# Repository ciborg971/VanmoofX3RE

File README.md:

# VanmoofX3RE

Big WIP, build at your own risk

- [OG contains information about original hardware](OG/README.md)

- [OSHW-Version is a fully open source redesign of the smart cardridge and battery BMS](OSHW-Version/README.md)

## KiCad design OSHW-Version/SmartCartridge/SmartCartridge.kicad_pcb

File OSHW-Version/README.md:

The led display is glued to the housing, charging port + original charger communication protocol will be hard to reverse, SIM slot + gsm antenna + backup battery are not needed so ... going for a 3D printed Smart Housing !

## 3D design of the smart cartridge housing

Still WIP
 
Online preview https://collaborate.shapr3d.com/v/ECH1UW3ffuTfgxgP5jvtE

All the cad is made on Shapr3d, if you need a file in a specific format create a github issue.

## BMS

Need to find compatible connector + cell specification

## SmartCartridge

Use the Pro-S3 from Unexpected Maker and I'm using [their kicad lib](https://github.com/UnexpectedMaker/esp32s3/tree/main)

Need to find compatible connector

Back 8 pin connector signals :

- GND
- Back light
- NC
- NC
- NC
- NC
- NC
- NC

Top front 10 pin connector signals :

- unknown
- unknown
- unknown
- GND
- unknown
- GND
- GND
- unknown
- unknown
- GND

Bottom front 12 pin connector signals :

- unknown
- GND
- unknown
- unknown
- unknown
- unknown
- GND
- unknown
- unknown
- unknown
- unknown
- unknown

Bottom front 10 pin connector signals :

- unknown
- GND
- unknown
- GND
- GND
- unknown
- unknown
- unknown
- GND
- unknown

## LedDisplay

166 WS2812-2020 RGB led (flexible pcb)
5V@6A peak

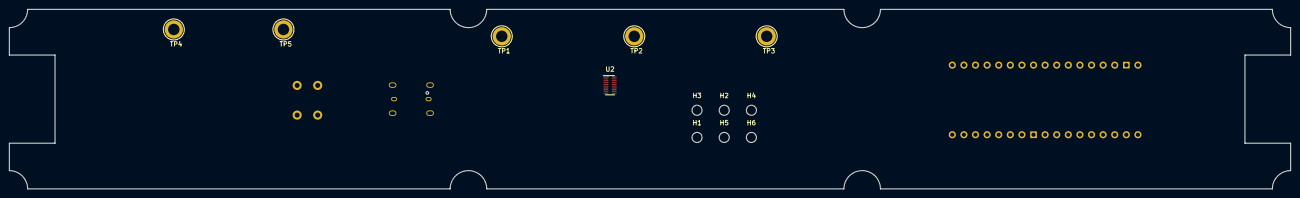
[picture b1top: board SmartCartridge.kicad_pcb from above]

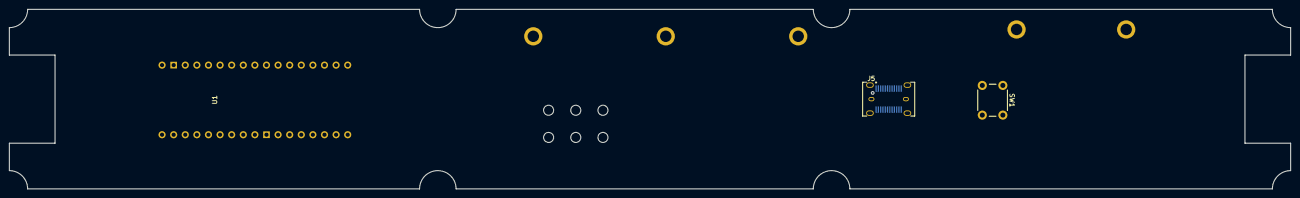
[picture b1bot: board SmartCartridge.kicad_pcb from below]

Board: 2 copper layers, 280.5 x 39.3 mm, 15 parts (3 on the bottom side), 2 nets, no tracks yet.

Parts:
H1, H2, H3, H4, H5, H6: MountingHole; MountingHole_2.2mm_M2
J5: USB_C_Receptacle; USB_C_Receptacle_JAE_DX07S024WJ1R350
SW1: SW_Push; SW_PUSH_6mm
TP1: BL1; TestPoint_Loop_D3.80mm_Drill2.5mm
TP2: BL2; TestPoint_Loop_D3.80mm_Drill2.5mm
TP3: BL3; TestPoint_Loop_D3.80mm_Drill2.5mm
TP4: VBAT-; TestPoint_Loop_D3.80mm_Drill2.5mm
TP5: VBAT+; TestPoint_Loop_D3.80mm_Drill2.5mm
U1: ProS3; ProS3_TH
U2: TXB0108DQSR; USON-20_2x4mm_P0.4mm

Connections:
unnamed: J5.A1 (GND), J5.A12 (GND), J5.B1 (GND), J5.B12 (GND)
unnamed: J5.A4 (VBUS), J5.A9 (VBUS), J5.B4 (VBUS), J5.B9 (VBUS)

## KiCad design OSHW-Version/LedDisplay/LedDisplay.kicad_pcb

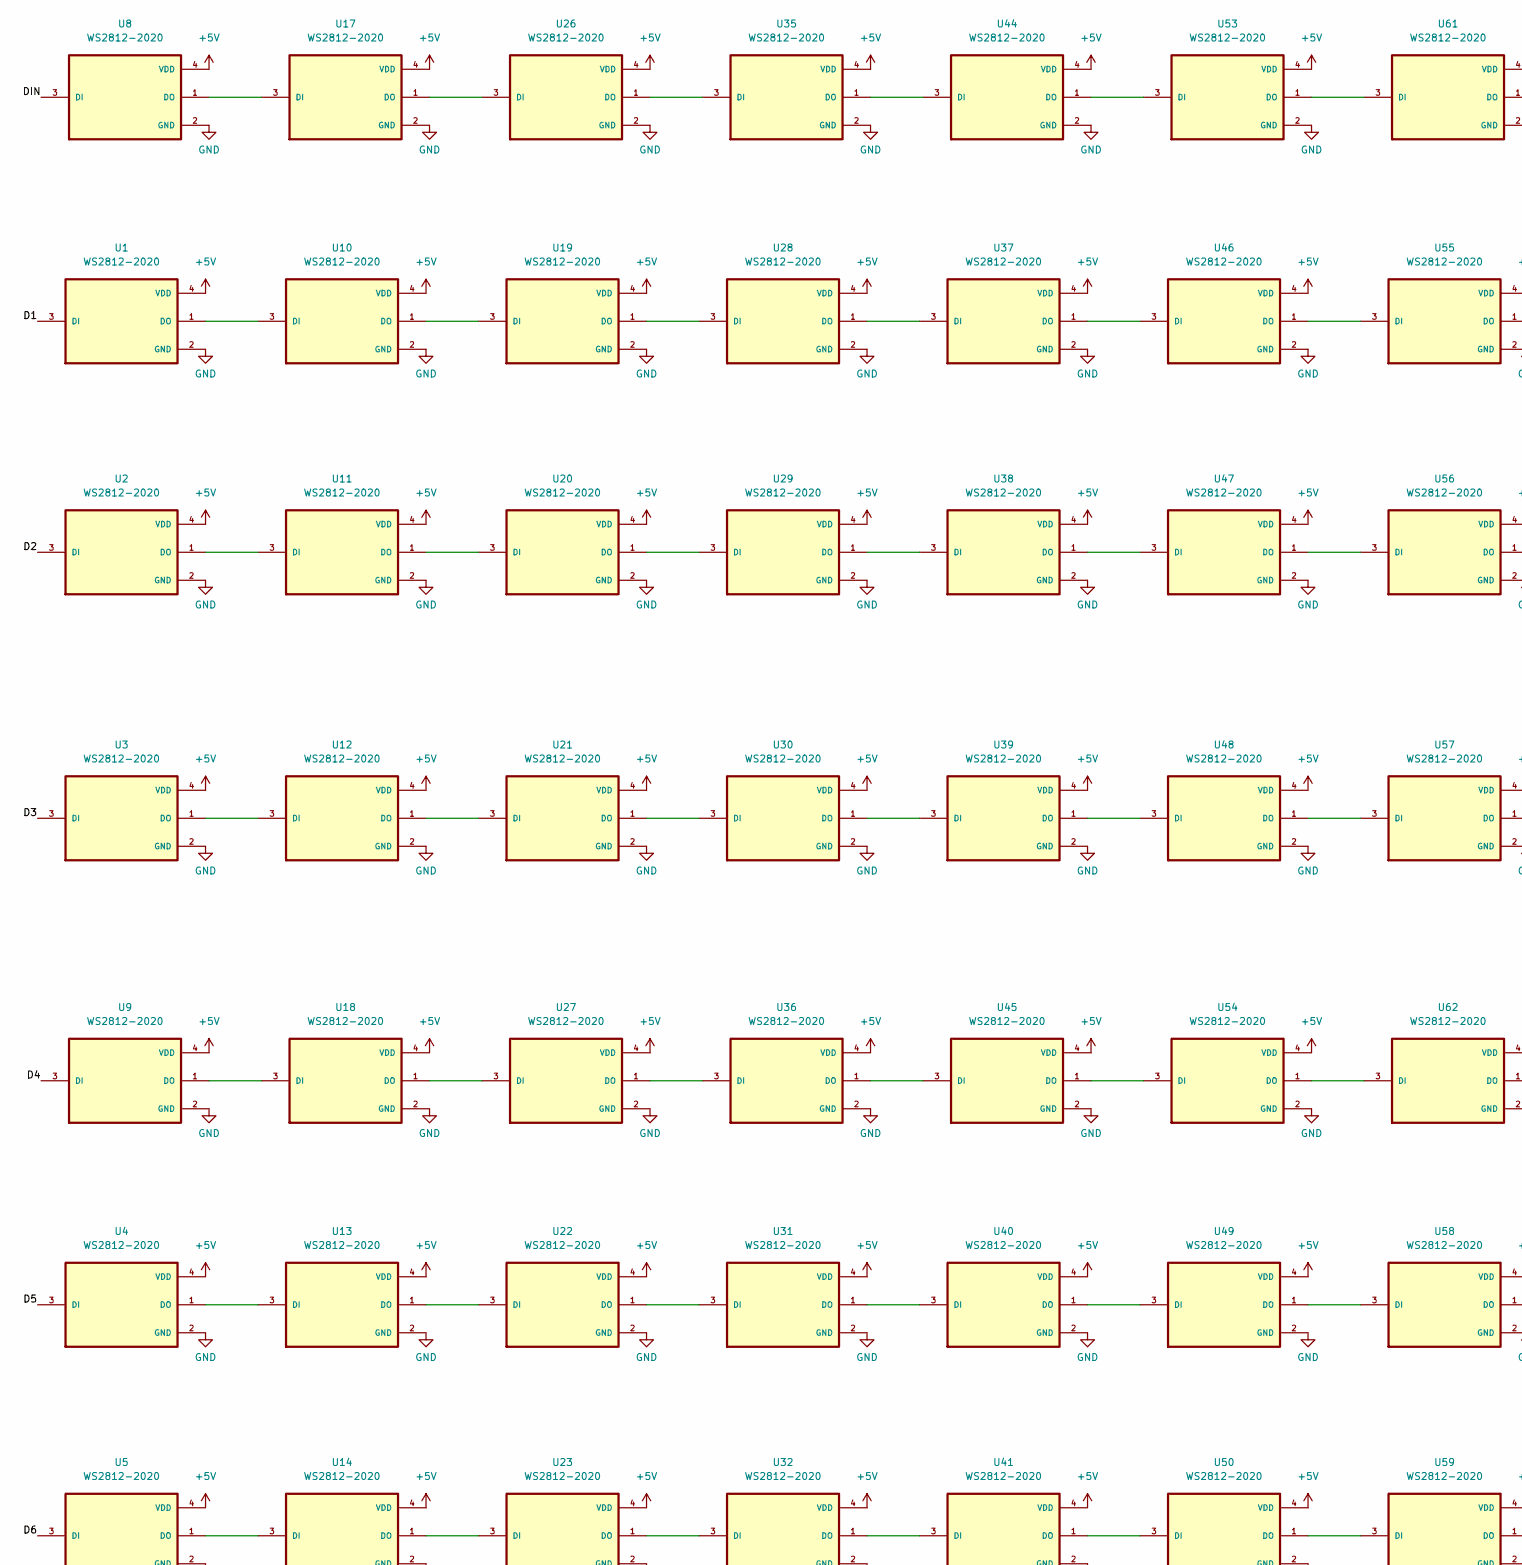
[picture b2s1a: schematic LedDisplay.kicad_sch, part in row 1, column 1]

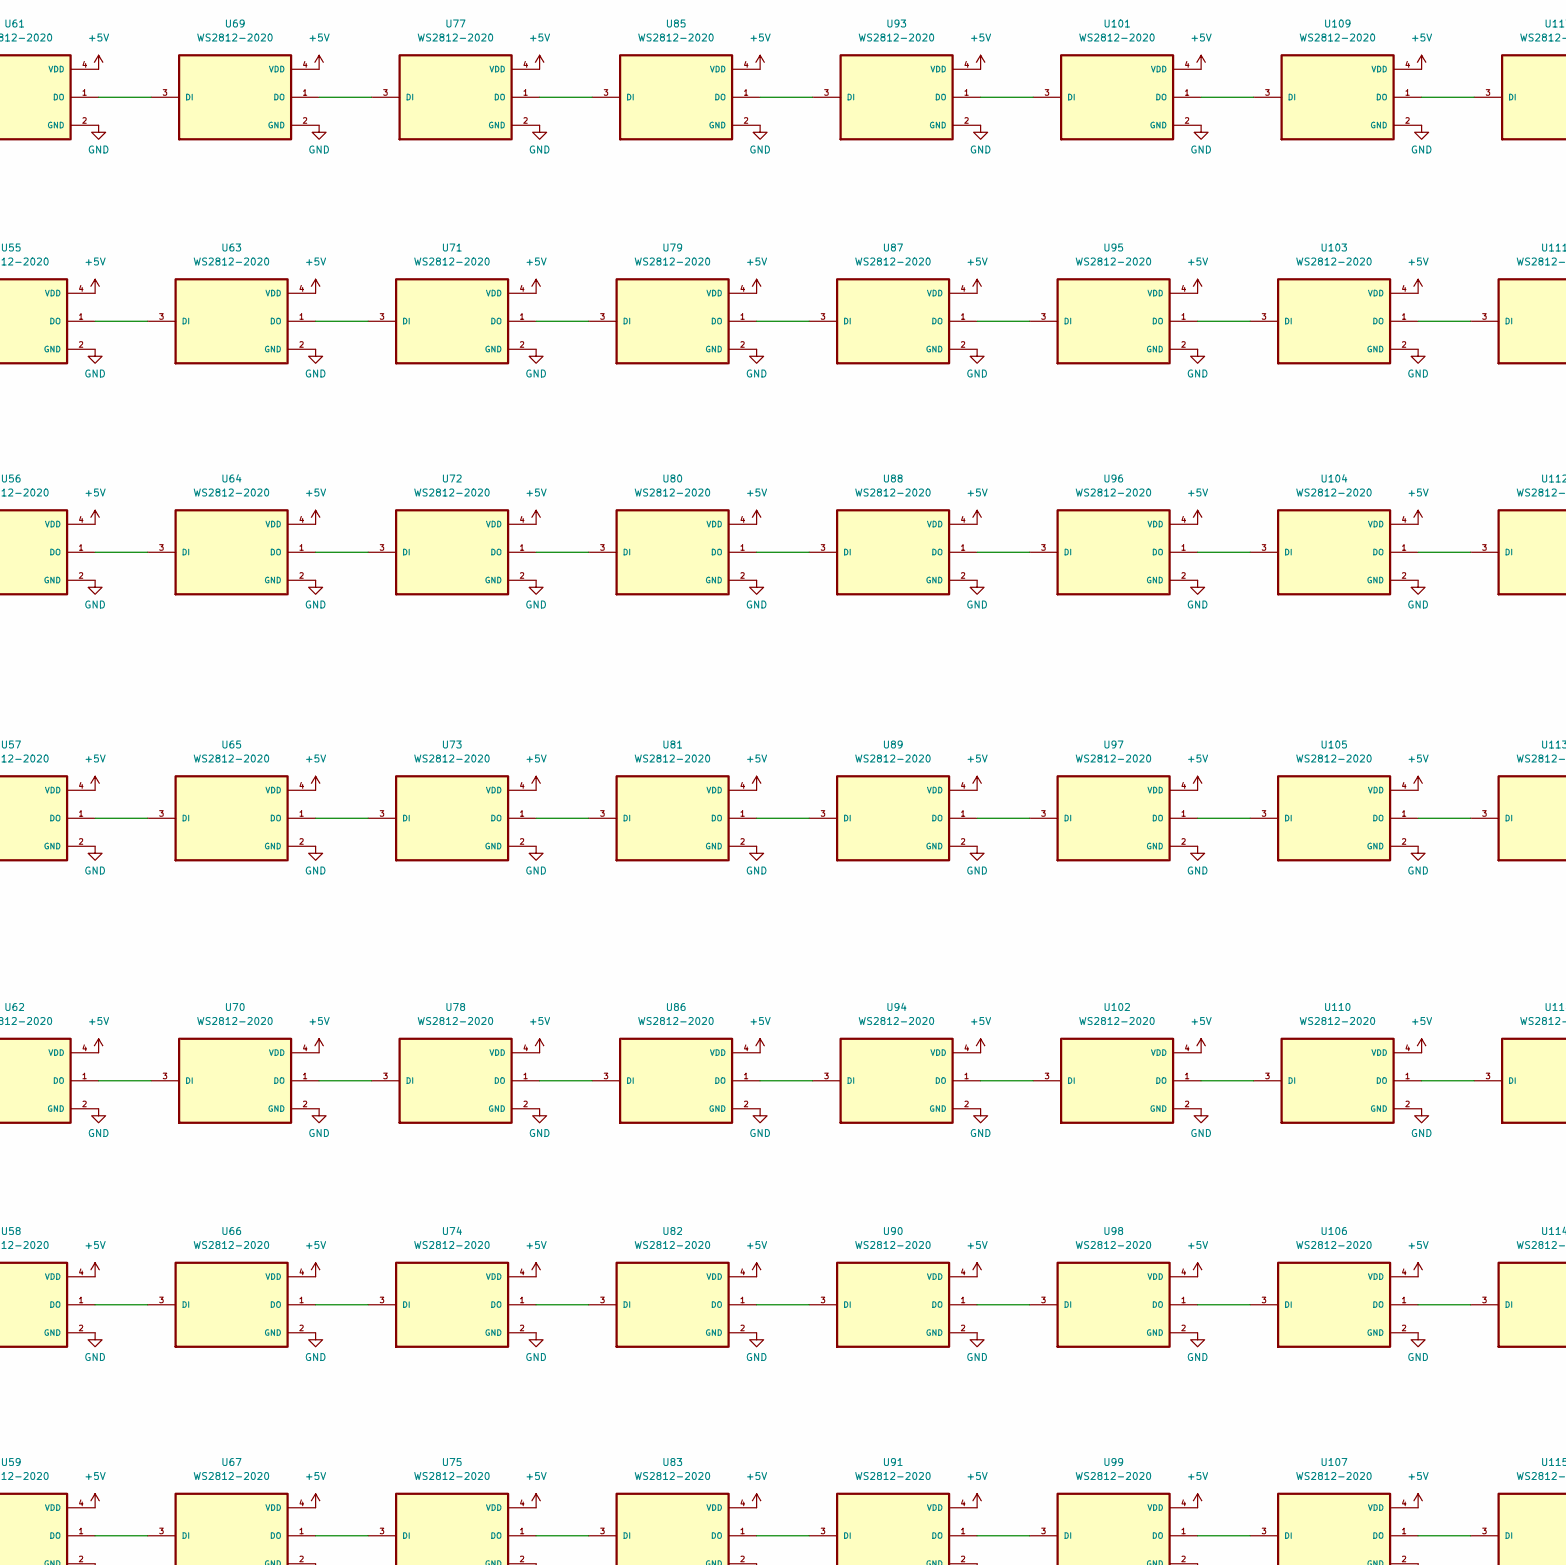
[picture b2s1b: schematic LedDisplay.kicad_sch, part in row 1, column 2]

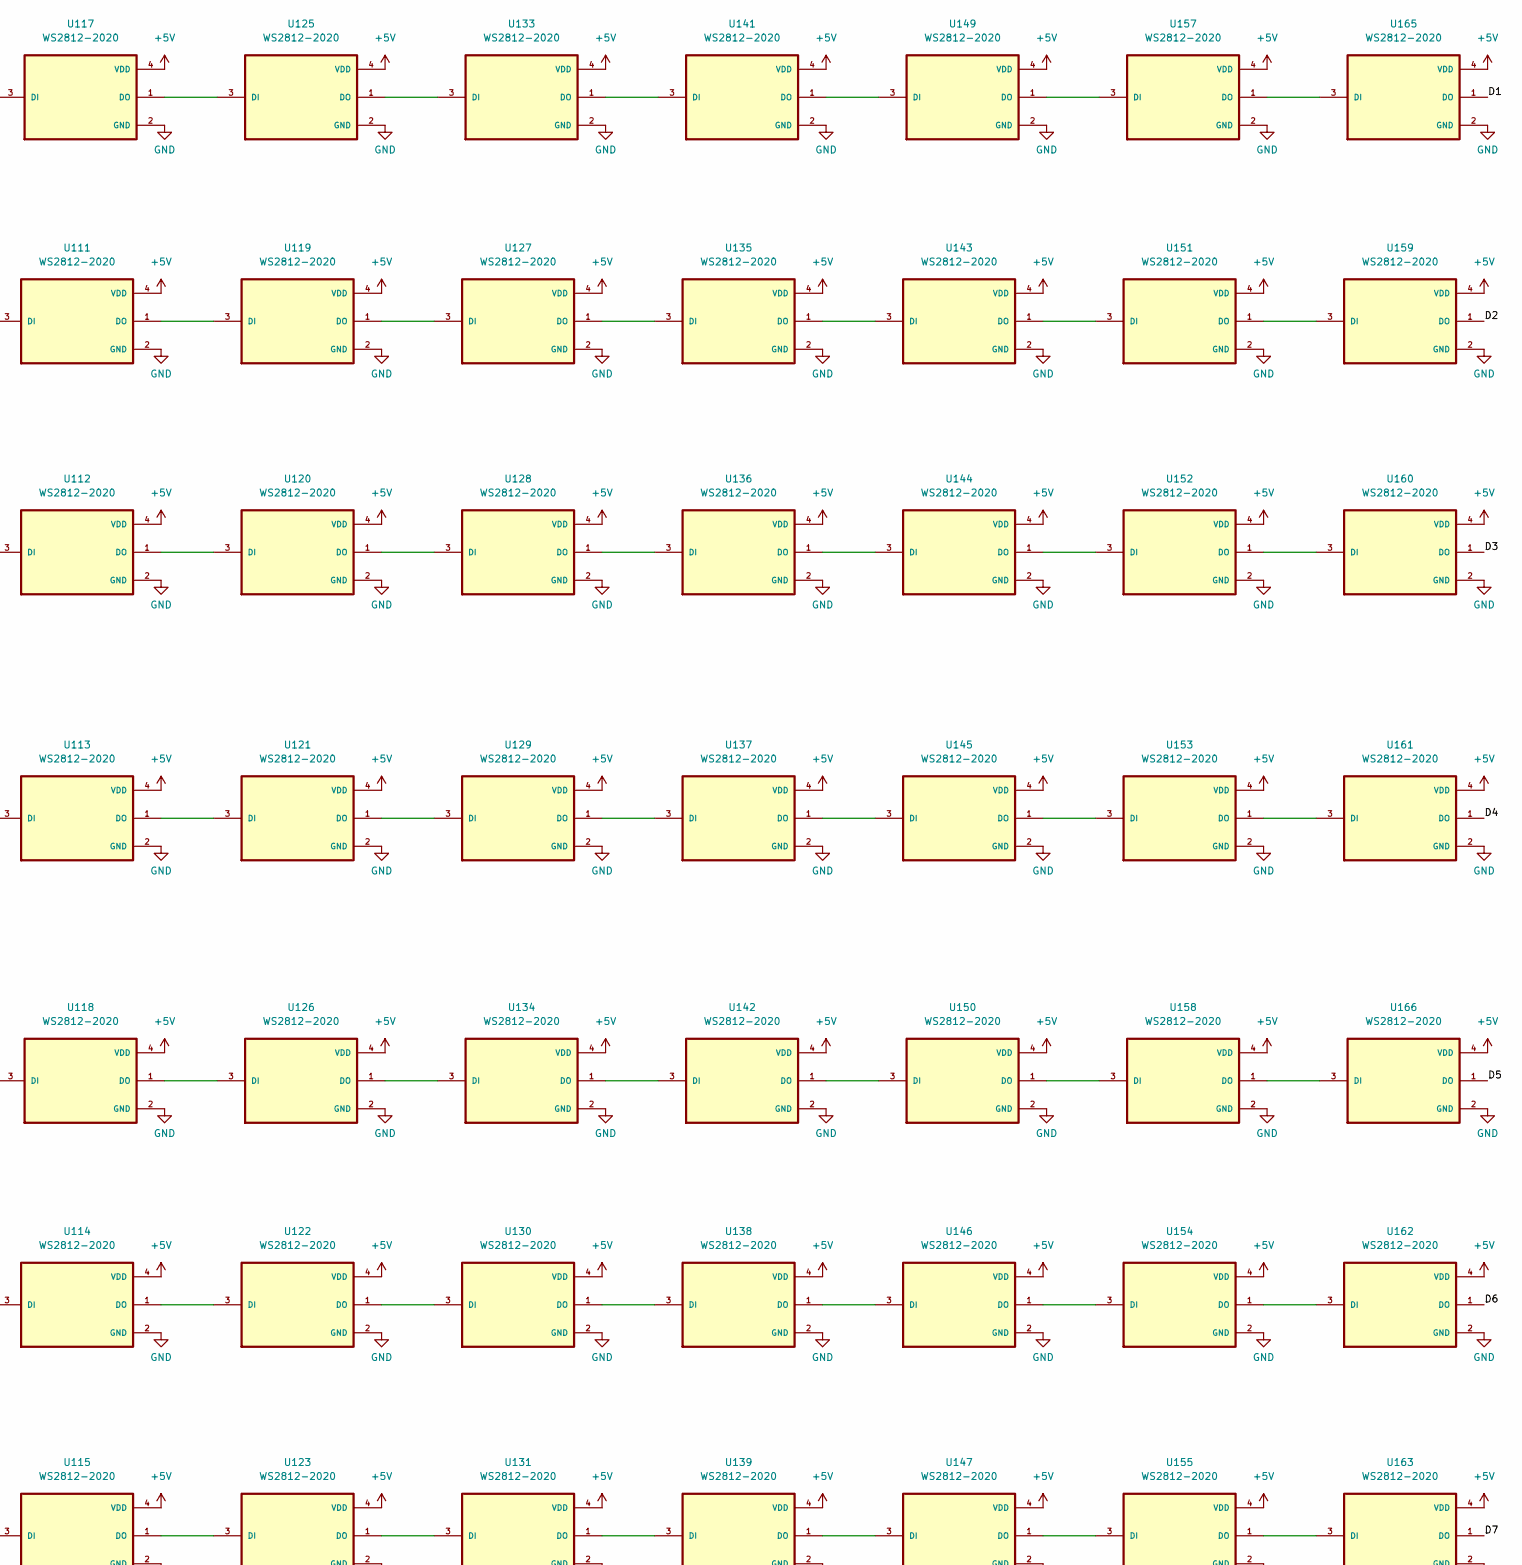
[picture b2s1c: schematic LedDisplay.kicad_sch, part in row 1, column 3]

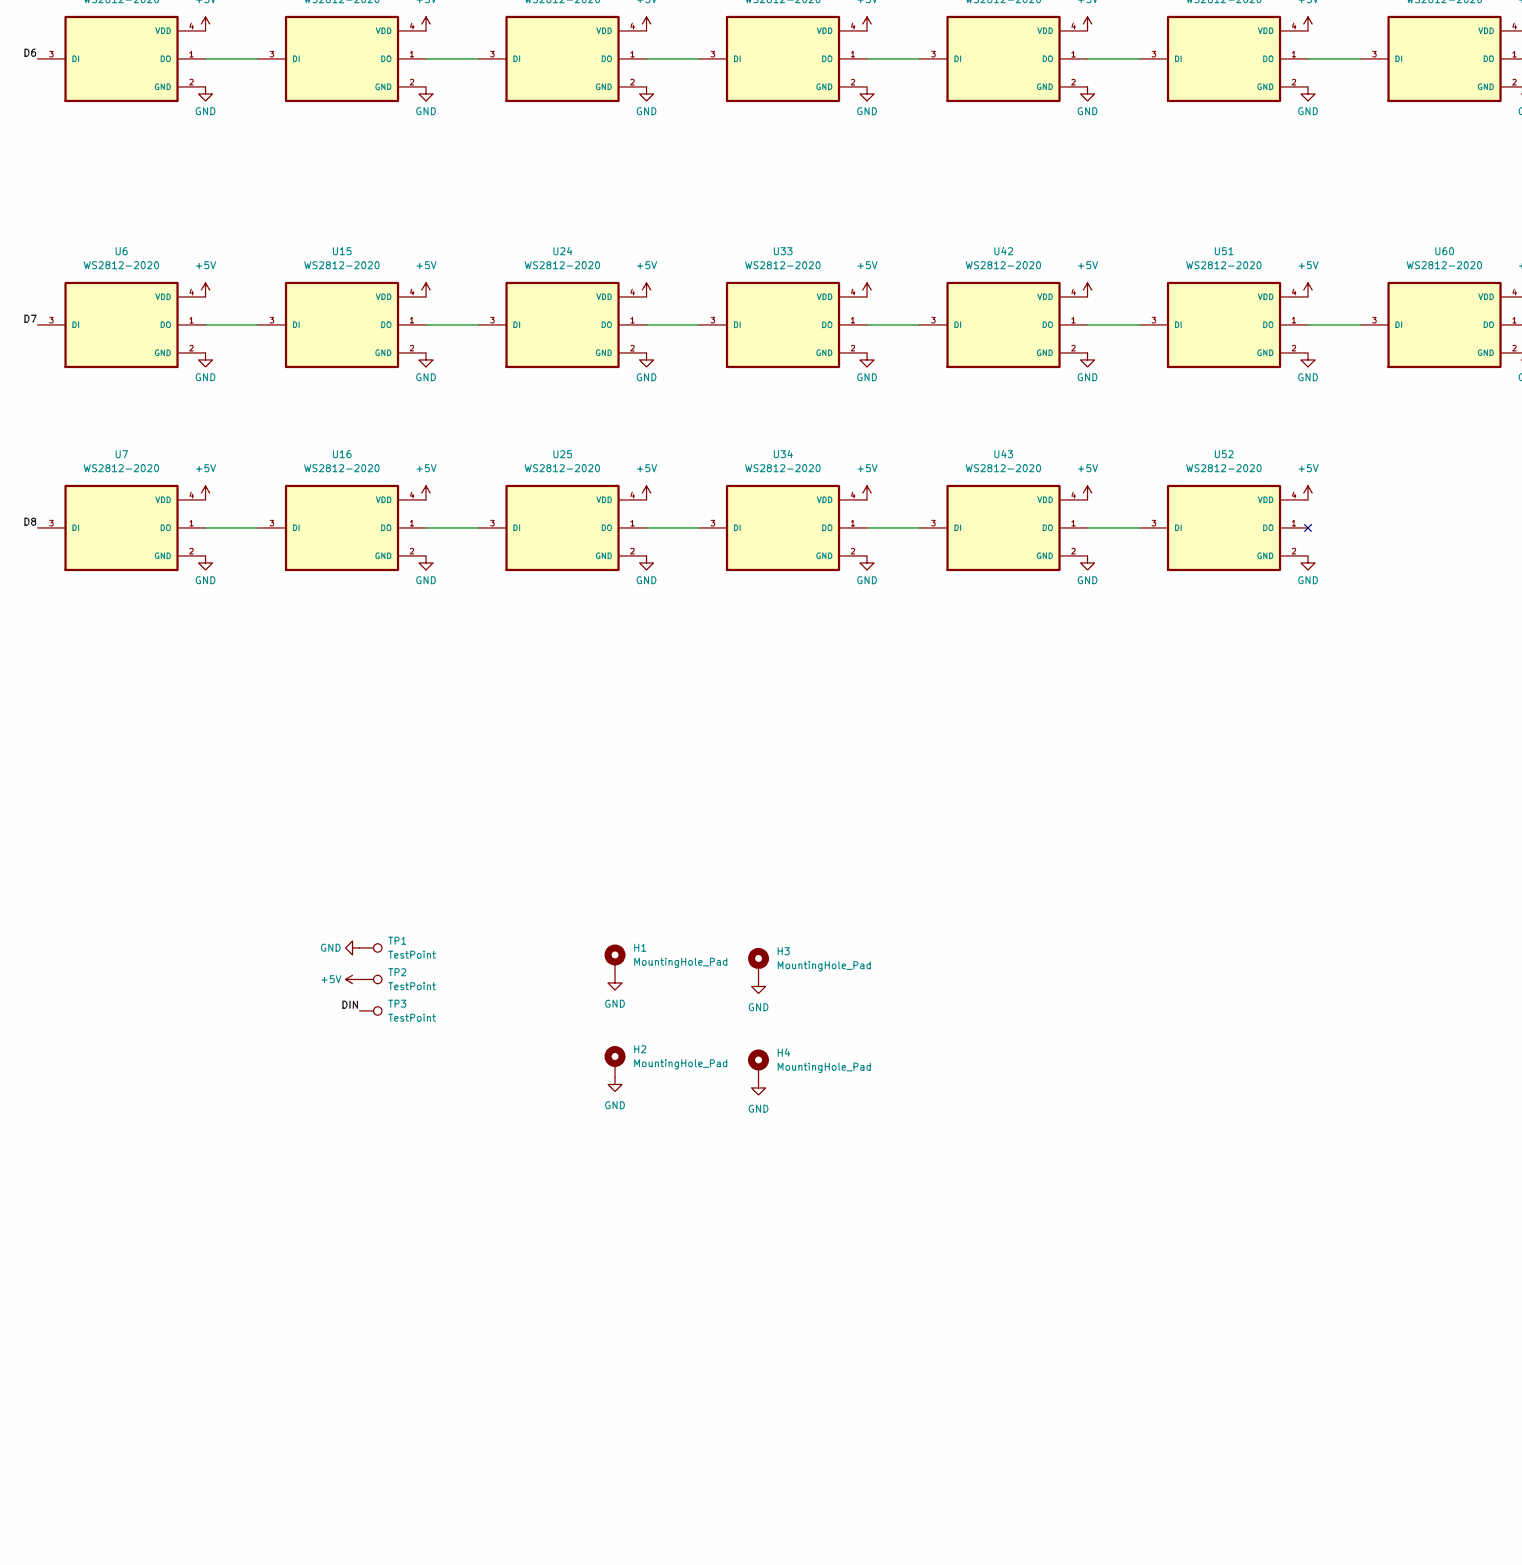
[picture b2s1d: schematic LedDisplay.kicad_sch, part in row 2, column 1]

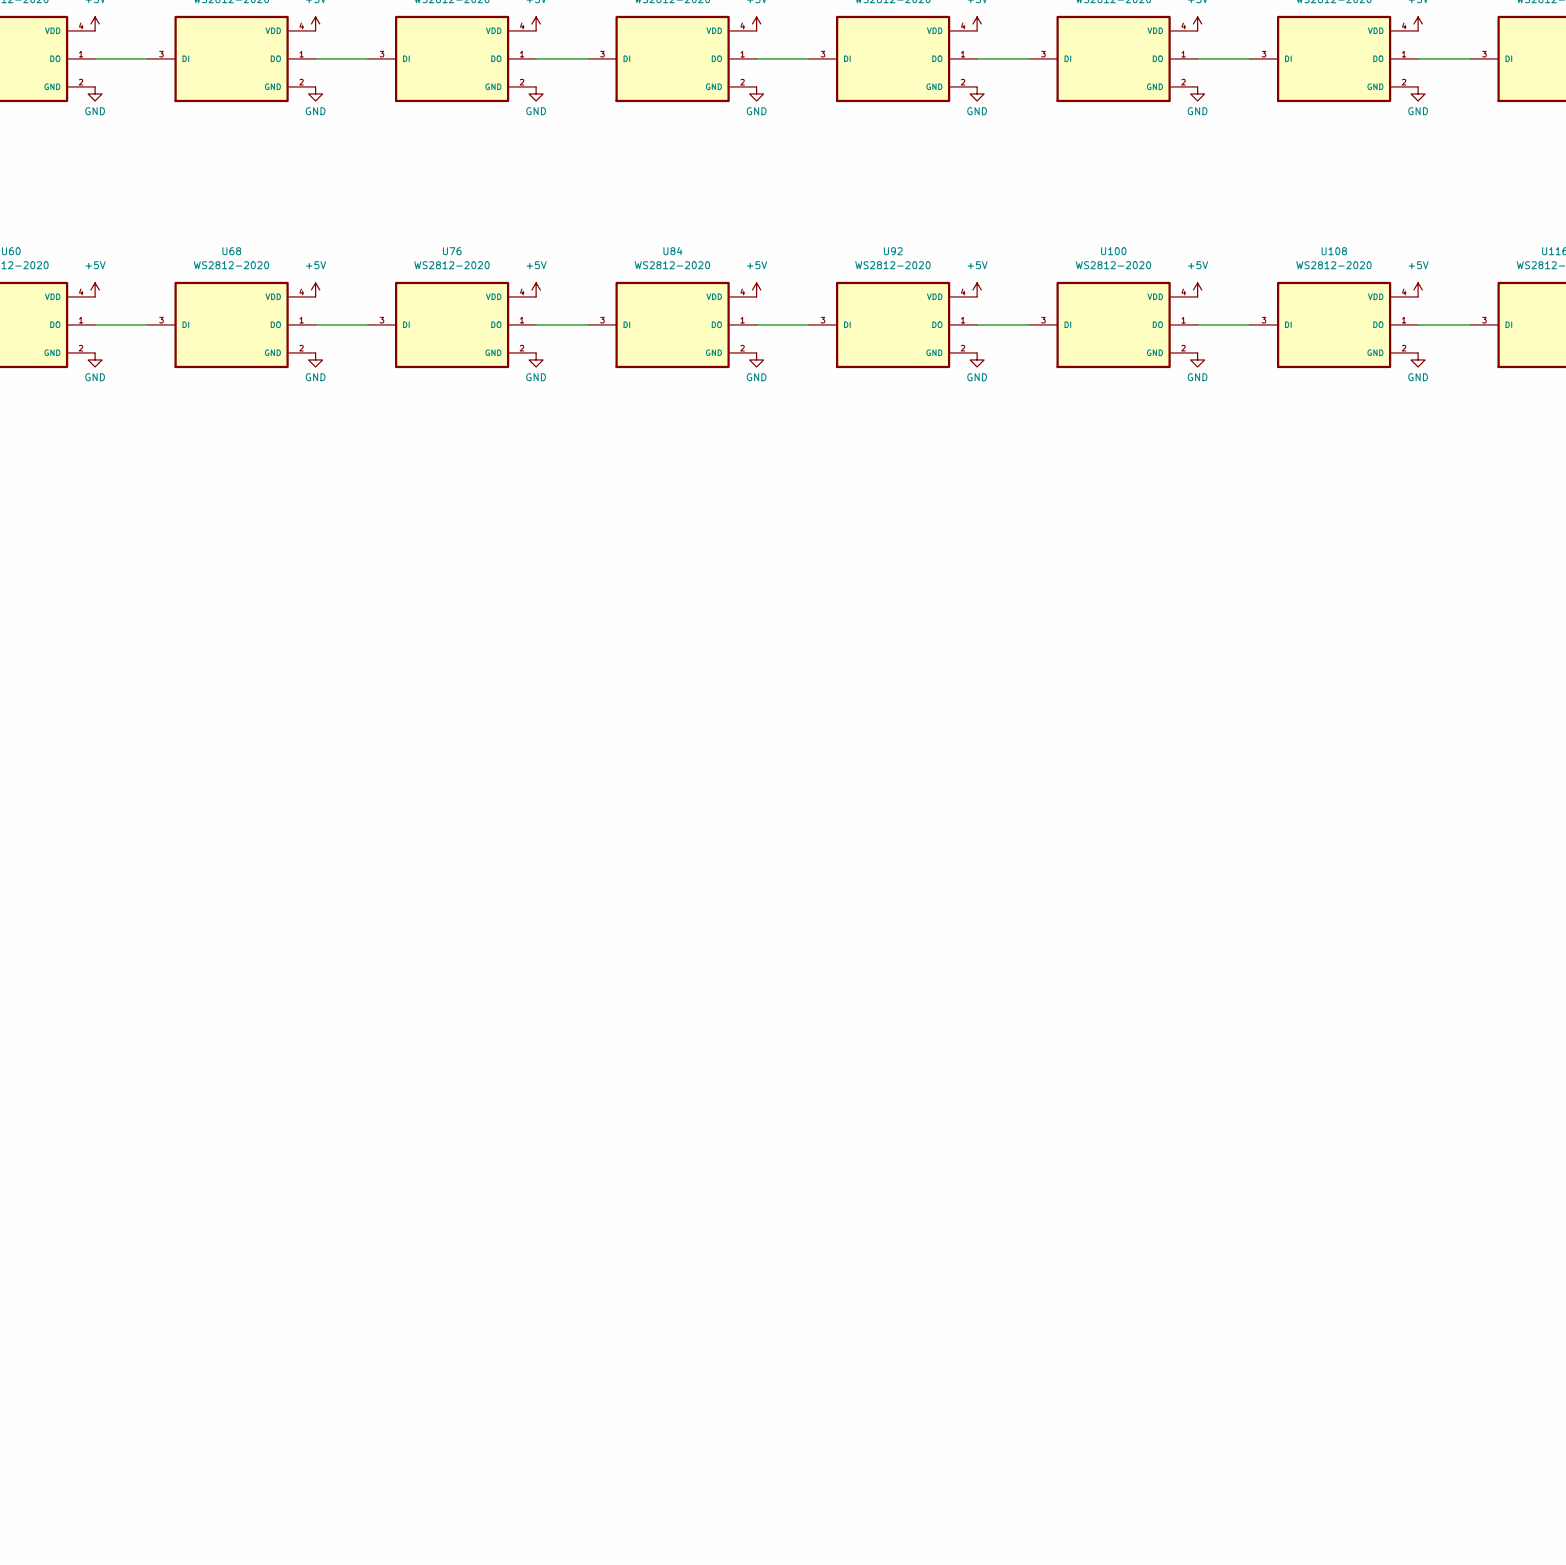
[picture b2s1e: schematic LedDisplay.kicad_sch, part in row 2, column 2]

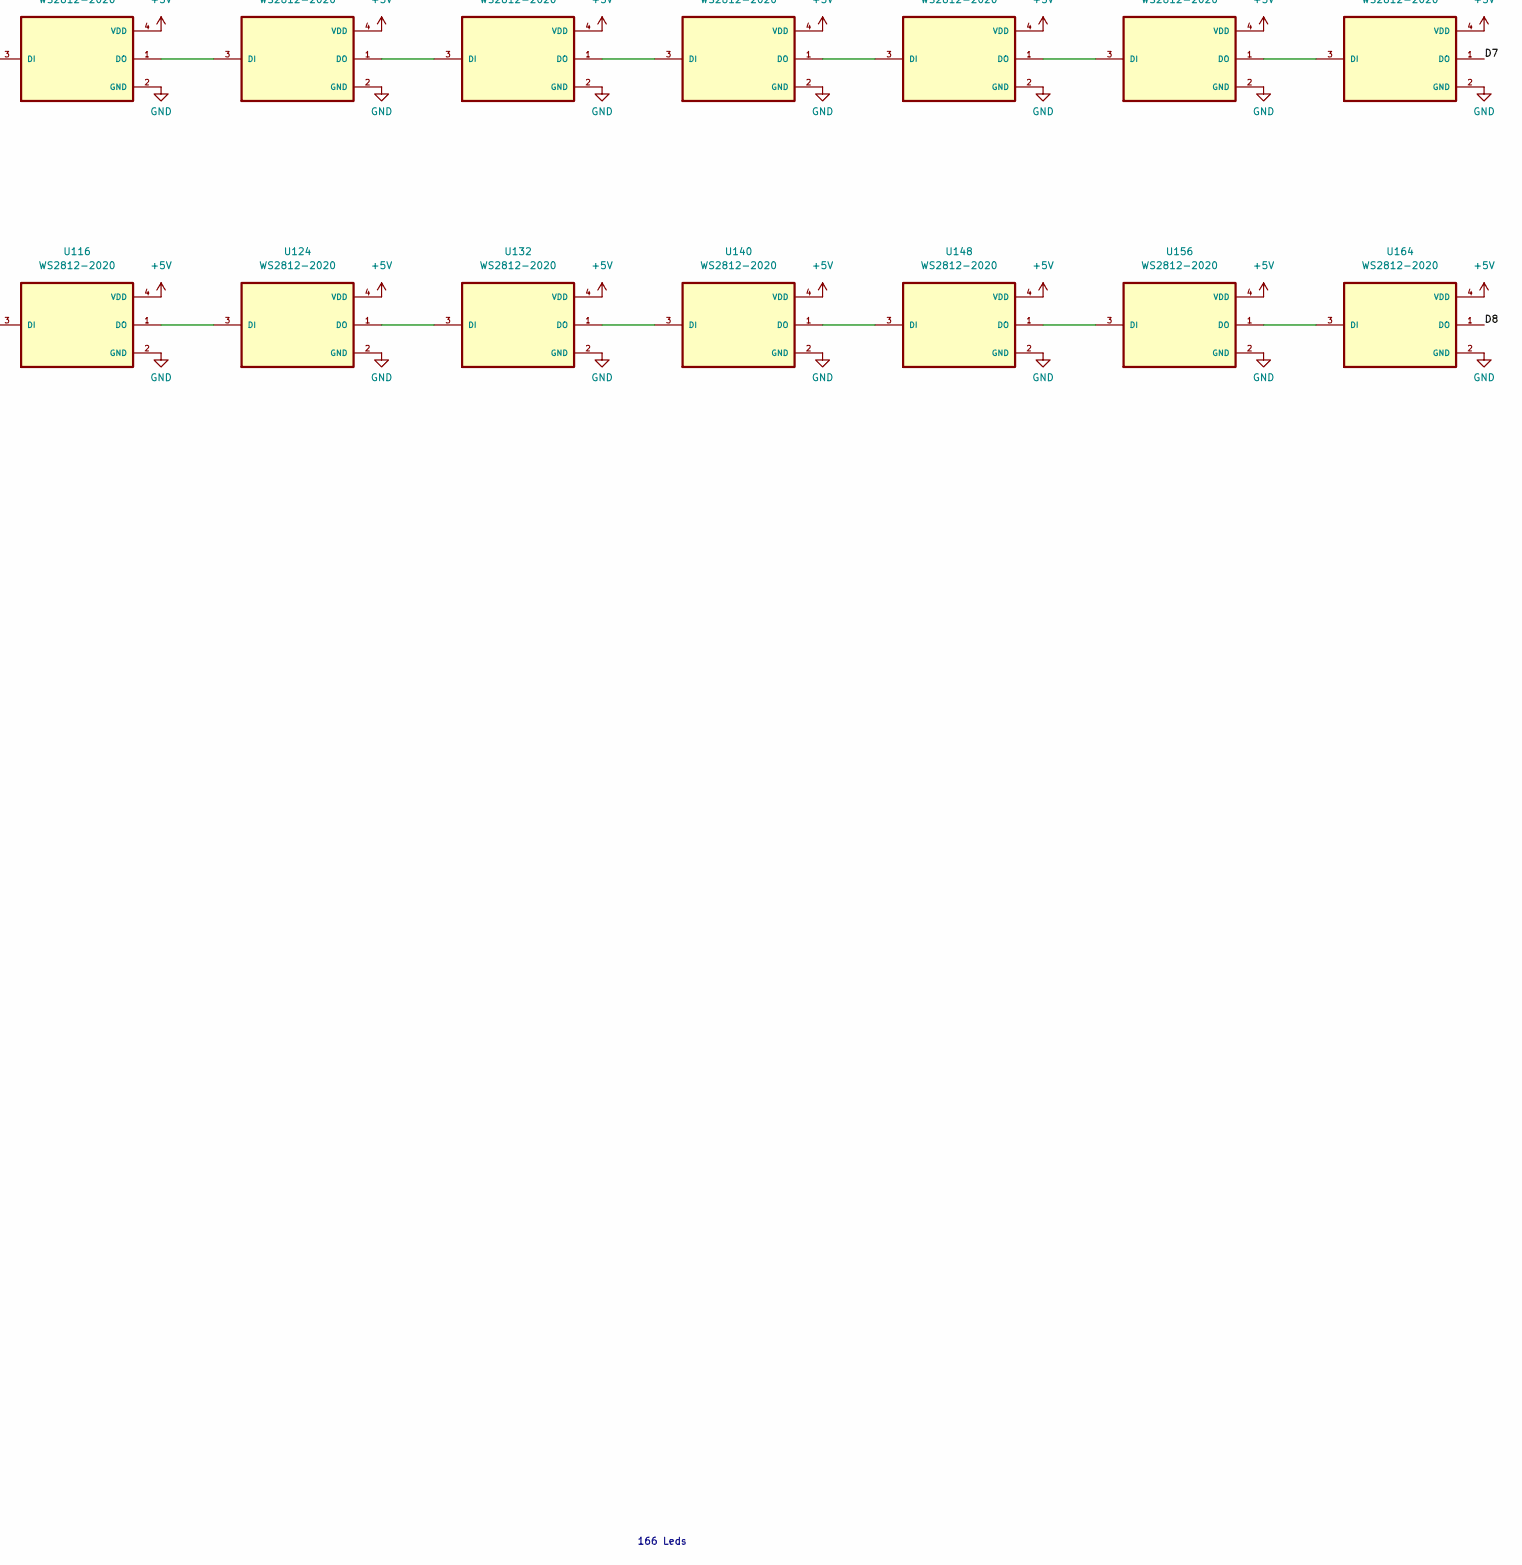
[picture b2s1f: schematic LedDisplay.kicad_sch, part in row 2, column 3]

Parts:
H1, H2, H3, H4: MountingHole_Pad; MountingHole_3.2mm_M3_DIN965_Pad
TP1, TP2, TP3: TestPoint; TestPoint_Pad_D3.0mm
U1, U2, U3, U4, U5, U6, U7, U8, U9, U10, U11, U12, U13, U14, U15, U16, U17, U18, U19, U20, U21, U22, U23, U24, U25, U26, U27, U28, U29, U30, U31, U32, U33, U34, U35, U36, U37, U38, U39, U40, U41, U42, U43, U44, U45, U46, U47, U48, U49, U50, U51, U52, U53, U54, U55, U56, U57, U58, U59, U60, U61, U62, U63, U64, U65, U66, U67, U68, U69, U70, U71, U72, U73, U74, U75, U76, U77, U78, U79, U80, U81, U82, U83, U84, U85, U86, U87, U88, U89, U90, U91, U92, U93, U94, U95, U96, U97, U98, U99, U100, U101, U102, U103, U104, U105, U106, U107, U108, U109, U110, U111, U112, U113, U114, U115, U116, U117, U118, U119, U120, U121, U122, U123, U124, U125, U126, U127, U128, U129, U130, U131, U132, U133, U134, U135, U136, U137, U138, U139, U140, U141, U142, U143, U144, U145, U146, U147, U148, U149, U150, U151, U152, U153, U154, U155, U156, U157, U158, U159, U160, U161, U162, U163, U164, U165, U166: WS2812-2020; LED_WS2812-2020; PARTREV V1.3

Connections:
+5V: TP2.1, U1.4 (VDD), U2.4 (VDD), U3.4 (VDD), U4.4 (VDD), U5.4 (VDD), U6.4 (VDD), U7.4 (VDD), U8.4 (VDD), U9.4 (VDD), U10.4 (VDD), U11.4 (VDD), U12.4 (VDD), U13.4 (VDD), U14.4 (VDD), U15.4 (VDD), U16.4 (VDD), U17.4 (VDD), U18.4 (VDD), U19.4 (VDD), U20.4 (VDD), U21.4 (VDD), U22.4 (VDD), U23.4 (VDD), U24.4 (VDD), U25.4 (VDD), U26.4 (VDD), U27.4 (VDD), U28.4 (VDD), U29.4 (VDD), U30.4 (VDD), U31.4 (VDD), U32.4 (VDD), U33.4 (VDD), U34.4 (VDD), U35.4 (VDD), U36.4 (VDD), U37.4 (VDD), U38.4 (VDD), U39.4 (VDD), U40.4 (VDD), U41.4 (VDD), U42.4 (VDD), U43.4 (VDD), U44.4 (VDD), U45.4 (VDD), U46.4 (VDD), U47.4 (VDD), U48.4 (VDD), U49.4 (VDD), U50.4 (VDD), U51.4 (VDD), U52.4 (VDD), U53.4 (VDD), U54.4 (VDD), U55.4 (VDD), U56.4 (VDD), U57.4 (VDD), U58.4 (VDD), U59.4 (VDD), U60.4 (VDD), U61.4 (VDD), U62.4 (VDD), U63.4 (VDD), U64.4 (VDD), U65.4 (VDD), U66.4 (VDD), U67.4 (VDD), U68.4 (VDD), U69.4 (VDD), U70.4 (VDD), U71.4 (VDD), U72.4 (VDD), U73.4 (VDD), U74.4 (VDD), U75.4 (VDD), U76.4 (VDD), U77.4 (VDD), U78.4 (VDD), U79.4 (VDD), U80.4 (VDD), U81.4 (VDD), U82.4 (VDD), U83.4 (VDD), U84.4 (VDD), U85.4 (VDD), U86.4 (VDD), U87.4 (VDD), U88.4 (VDD), U89.4 (VDD), U90.4 (VDD), U91.4 (VDD), U92.4 (VDD), U93.4 (VDD), U94.4 (VDD), U95.4 (VDD), U96.4 (VDD), U97.4 (VDD), U98.4 (VDD), U99.4 (VDD), U100.4 (VDD), U101.4 (VDD), U102.4 (VDD), U103.4 (VDD), U104.4 (VDD), U105.4 (VDD), U106.4 (VDD), U107.4 (VDD), U108.4 (VDD), U109.4 (VDD), U110.4 (VDD), U111.4 (VDD), U112.4 (VDD), U113.4 (VDD), U114.4 (VDD), U115.4 (VDD), U116.4 (VDD), U117.4 (VDD), U118.4 (VDD), U119.4 (VDD), U120.4 (VDD), U121.4 (VDD), U122.4 (VDD), U123.4 (VDD), U124.4 (VDD), U125.4 (VDD), U126.4 (VDD), U127.4 (VDD), U128.4 (VDD), U129.4 (VDD), U130.4 (VDD), U131.4 (VDD), U132.4 (VDD), U133.4 (VDD), U134.4 (VDD), U135.4 (VDD), U136.4 (VDD), U137.4 (VDD), U138.4 (VDD), U139.4 (VDD), U140.4 (VDD), U141.4 (VDD), U142.4 (VDD), U143.4 (VDD), U144.4 (VDD), U145.4 (VDD), U146.4 (VDD), U147.4 (VDD), U148.4 (VDD), U149.4 (VDD), U150.4 (VDD), U151.4 (VDD), U152.4 (VDD), U153.4 (VDD), U154.4 (VDD), U155.4 (VDD), U156.4 (VDD), U157.4 (VDD), U158.4 (VDD), U159.4 (VDD), U160.4 (VDD), U161.4 (VDD), U162.4 (VDD), U163.4 (VDD), U164.4 (VDD), U165.4 (VDD), U166.4 (VDD)
/D1: U1.3 (DI), U165.1 (DO)
/D2: U2.3 (DI), U159.1 (DO)
/D3: U3.3 (DI), U160.1 (DO)
/D4: U9.3 (DI), U161.1 (DO)
/D5: U4.3 (DI), U166.1 (DO)
/D6: U5.3 (DI), U162.1 (DO)
/D7: U6.3 (DI), U163.1 (DO)
/D8: U7.3 (DI), U164.1 (DO)
/DIN: TP3.1, U8.3 (DI)
GND: H1.1, H2.1, H3.1, H4.1, TP1.1, U1.2 (GND), U2.2 (GND), U3.2 (GND), U4.2 (GND), U5.2 (GND), U6.2 (GND), U7.2 (GND), U8.2 (GND), U9.2 (GND), U10.2 (GND), U11.2 (GND), U12.2 (GND), U13.2 (GND), U14.2 (GND), U15.2 (GND), U16.2 (GND), U17.2 (GND), U18.2 (GND), U19.2 (GND), U20.2 (GND), U21.2 (GND), U22.2 (GND), U23.2 (GND), U24.2 (GND), U25.2 (GND), U26.2 (GND), U27.2 (GND), U28.2 (GND), U29.2 (GND), U30.2 (GND), U31.2 (GND), U32.2 (GND), U33.2 (GND), U34.2 (GND), U35.2 (GND), U36.2 (GND), U37.2 (GND), U38.2 (GND), U39.2 (GND), U40.2 (GND), U41.2 (GND), U42.2 (GND), U43.2 (GND), U44.2 (GND), U45.2 (GND), U46.2 (GND), U47.2 (GND), U48.2 (GND), U49.2 (GND), U50.2 (GND), U51.2 (GND), U52.2 (GND), U53.2 (GND), U54.2 (GND), U55.2 (GND), U56.2 (GND), U57.2 (GND), U58.2 (GND), U59.2 (GND), U60.2 (GND), U61.2 (GND), U62.2 (GND), U63.2 (GND), U64.2 (GND), U65.2 (GND), U66.2 (GND), U67.2 (GND), U68.2 (GND), U69.2 (GND), U70.2 (GND), U71.2 (GND), U72.2 (GND), U73.2 (GND), U74.2 (GND), U75.2 (GND), U76.2 (GND), U77.2 (GND), U78.2 (GND), U79.2 (GND), U80.2 (GND), U81.2 (GND), U82.2 (GND), U83.2 (GND), U84.2 (GND), U85.2 (GND), U86.2 (GND), U87.2 (GND), U88.2 (GND), U89.2 (GND), U90.2 (GND), U91.2 (GND), U92.2 (GND), U93.2 (GND), U94.2 (GND), U95.2 (GND), U96.2 (GND), U97.2 (GND), U98.2 (GND), U99.2 (GND), U100.2 (GND), U101.2 (GND), U102.2 (GND), U103.2 (GND), U104.2 (GND), U105.2 (GND), U106.2 (GND), U107.2 (GND), U108.2 (GND), U109.2 (GND), U110.2 (GND), U111.2 (GND), U112.2 (GND), U113.2 (GND), U114.2 (GND), U115.2 (GND), U116.2 (GND), U117.2 (GND), U118.2 (GND), U119.2 (GND), U120.2 (GND), U121.2 (GND), U122.2 (GND), U123.2 (GND), U124.2 (GND), U125.2 (GND), U126.2 (GND), U127.2 (GND), U128.2 (GND), U129.2 (GND), U130.2 (GND), U131.2 (GND), U132.2 (GND), U133.2 (GND), U134.2 (GND), U135.2 (GND), U136.2 (GND), U137.2 (GND), U138.2 (GND), U139.2 (GND), U140.2 (GND), U141.2 (GND), U142.2 (GND), U143.2 (GND), U144.2 (GND), U145.2 (GND), U146.2 (GND), U147.2 (GND), U148.2 (GND), U149.2 (GND), U150.2 (GND), U151.2 (GND), U152.2 (GND), U153.2 (GND), U154.2 (GND), U155.2 (GND), U156.2 (GND), U157.2 (GND), U158.2 (GND), U159.2 (GND), U160.2 (GND), U161.2 (GND), U162.2 (GND), U163.2 (GND), U164.2 (GND), U165.2 (GND), U166.2 (GND)
unnamed: U1.1 (DO), U10.3 (DI)
unnamed: U10.1 (DO), U19.3 (DI)
unnamed: U11.1 (DO), U20.3 (DI)
unnamed: U2.1 (DO), U11.3 (DI)
unnamed: U12.1 (DO), U21.3 (DI)
unnamed: U3.1 (DO), U12.3 (DI)
unnamed: U13.1 (DO), U22.3 (DI)
unnamed: U4.1 (DO), U13.3 (DI)
unnamed: U14.1 (DO), U23.3 (DI)
unnamed: U5.1 (DO), U14.3 (DI)
unnamed: U15.1 (DO), U24.3 (DI)
unnamed: U6.1 (DO), U15.3 (DI)
unnamed: U16.1 (DO), U25.3 (DI)
unnamed: U7.1 (DO), U16.3 (DI)
unnamed: U17.1 (DO), U26.3 (DI)
unnamed: U8.1 (DO), U17.3 (DI)
unnamed: U18.1 (DO), U27.3 (DI)
unnamed: U9.1 (DO), U18.3 (DI)
unnamed: U19.1 (DO), U28.3 (DI)
unnamed: U20.1 (DO), U29.3 (DI)
unnamed: U21.1 (DO), U30.3 (DI)
unnamed: U22.1 (DO), U31.3 (DI)
unnamed: U23.1 (DO), U32.3 (DI)
unnamed: U24.1 (DO), U33.3 (DI)
unnamed: U25.1 (DO), U34.3 (DI)
unnamed: U26.1 (DO), U35.3 (DI)
unnamed: U27.1 (DO), U36.3 (DI)
unnamed: U28.1 (DO), U37.3 (DI)
unnamed: U29.1 (DO), U38.3 (DI)
unnamed: U30.1 (DO), U39.3 (DI)
unnamed: U31.1 (DO), U40.3 (DI)
unnamed: U32.1 (DO), U41.3 (DI)
unnamed: U33.1 (DO), U42.3 (DI)
unnamed: U34.1 (DO), U43.3 (DI)
unnamed: U35.1 (DO), U44.3 (DI)
unnamed: U36.1 (DO), U45.3 (DI)
unnamed: U37.1 (DO), U46.3 (DI)
unnamed: U38.1 (DO), U47.3 (DI)
unnamed: U39.1 (DO), U48.3 (DI)
unnamed: U40.1 (DO), U49.3 (DI)
unnamed: U41.1 (DO), U50.3 (DI)
unnamed: U42.1 (DO), U51.3 (DI)
unnamed: U43.1 (DO), U52.3 (DI)
unnamed: U44.1 (DO), U53.3 (DI)
unnamed: U45.1 (DO), U54.3 (DI)
unnamed: U46.1 (DO), U55.3 (DI)
unnamed: U47.1 (DO), U56.3 (DI)
unnamed: U48.1 (DO), U57.3 (DI)
unnamed: U49.1 (DO), U58.3 (DI)
unnamed: U50.1 (DO), U59.3 (DI)
unnamed: U51.1 (DO), U60.3 (DI)
unnamed: U53.1 (DO), U61.3 (DI)
unnamed: U54.1 (DO), U62.3 (DI)
unnamed: U55.1 (DO), U63.3 (DI)
unnamed: U56.1 (DO), U64.3 (DI)
unnamed: U57.1 (DO), U65.3 (DI)
unnamed: U58.1 (DO), U66.3 (DI)
unnamed: U59.1 (DO), U67.3 (DI)
unnamed: U60.1 (DO), U68.3 (DI)
unnamed: U61.1 (DO), U69.3 (DI)
unnamed: U62.1 (DO), U70.3 (DI)
unnamed: U63.1 (DO), U71.3 (DI)
unnamed: U64.1 (DO), U72.3 (DI)
unnamed: U65.1 (DO), U73.3 (DI)
unnamed: U66.1 (DO), U74.3 (DI)
unnamed: U67.1 (DO), U75.3 (DI)
unnamed: U68.1 (DO), U76.3 (DI)
unnamed: U69.1 (DO), U77.3 (DI)
unnamed: U70.1 (DO), U78.3 (DI)
unnamed: U71.1 (DO), U79.3 (DI)
unnamed: U72.1 (DO), U80.3 (DI)
unnamed: U73.1 (DO), U81.3 (DI)
unnamed: U74.1 (DO), U82.3 (DI)
unnamed: U75.1 (DO), U83.3 (DI)
unnamed: U76.1 (DO), U84.3 (DI)
unnamed: U77.1 (DO), U85.3 (DI)
unnamed: U78.1 (DO), U86.3 (DI)
unnamed: U79.1 (DO), U87.3 (DI)
unnamed: U80.1 (DO), U88.3 (DI)
unnamed: U81.1 (DO), U89.3 (DI)
unnamed: U82.1 (DO), U90.3 (DI)
unnamed: U83.1 (DO), U91.3 (DI)
unnamed: U84.1 (DO), U92.3 (DI)
unnamed: U85.1 (DO), U93.3 (DI)
unnamed: U86.1 (DO), U94.3 (DI)
unnamed: U87.1 (DO), U95.3 (DI)
unnamed: U88.1 (DO), U96.3 (DI)
unnamed: U89.1 (DO), U97.3 (DI)
unnamed: U90.1 (DO), U98.3 (DI)
unnamed: U91.1 (DO), U99.3 (DI)
unnamed: U100.1 (DO), U108.3 (DI)
unnamed: U92.1 (DO), U100.3 (DI)
unnamed: U101.1 (DO), U109.3 (DI)
unnamed: U93.1 (DO), U101.3 (DI)
unnamed: U102.1 (DO), U110.3 (DI)
unnamed: U94.1 (DO), U102.3 (DI)
unnamed: U103.1 (DO), U111.3 (DI)
unnamed: U95.1 (DO), U103.3 (DI)
unnamed: U104.1 (DO), U112.3 (DI)
unnamed: U96.1 (DO), U104.3 (DI)
unnamed: U105.1 (DO), U113.3 (DI)
unnamed: U97.1 (DO), U105.3 (DI)
unnamed: U106.1 (DO), U114.3 (DI)
unnamed: U98.1 (DO), U106.3 (DI)
unnamed: U107.1 (DO), U115.3 (DI)
unnamed: U99.1 (DO), U107.3 (DI)
unnamed: U108.1 (DO), U116.3 (DI)
unnamed: U109.1 (DO), U117.3 (DI)
unnamed: U110.1 (DO), U118.3 (DI)
unnamed: U111.1 (DO), U119.3 (DI)
unnamed: U112.1 (DO), U120.3 (DI)
unnamed: U113.1 (DO), U121.3 (DI)
unnamed: U114.1 (DO), U122.3 (DI)
unnamed: U115.1 (DO), U123.3 (DI)
unnamed: U116.1 (DO), U124.3 (DI)
unnamed: U117.1 (DO), U125.3 (DI)
unnamed: U118.1 (DO), U126.3 (DI)
unnamed: U119.1 (DO), U127.3 (DI)
unnamed: U120.1 (DO), U128.3 (DI)
unnamed: U121.1 (DO), U129.3 (DI)
unnamed: U122.1 (DO), U130.3 (DI)
unnamed: U123.1 (DO), U131.3 (DI)
unnamed: U124.1 (DO), U132.3 (DI)
unnamed: U125.1 (DO), U133.3 (DI)
unnamed: U126.1 (DO), U134.3 (DI)
unnamed: U127.1 (DO), U135.3 (DI)
unnamed: U128.1 (DO), U136.3 (DI)
unnamed: U129.1 (DO), U137.3 (DI)
unnamed: U130.1 (DO), U138.3 (DI)
unnamed: U131.1 (DO), U139.3 (DI)
unnamed: U132.1 (DO), U140.3 (DI)
unnamed: U133.1 (DO), U141.3 (DI)
unnamed: U134.1 (DO), U142.3 (DI)
unnamed: U135.1 (DO), U143.3 (DI)
unnamed: U136.1 (DO), U144.3 (DI)
unnamed: U137.1 (DO), U145.3 (DI)
unnamed: U138.1 (DO), U146.3 (DI)
unnamed: U139.1 (DO), U147.3 (DI)
unnamed: U140.1 (DO), U148.3 (DI)
unnamed: U141.1 (DO), U149.3 (DI)
unnamed: U142.1 (DO), U150.3 (DI)
unnamed: U143.1 (DO), U151.3 (DI)
unnamed: U144.1 (DO), U152.3 (DI)
unnamed: U145.1 (DO), U153.3 (DI)
unnamed: U146.1 (DO), U154.3 (DI)
unnamed: U147.1 (DO), U155.3 (DI)
unnamed: U148.1 (DO), U156.3 (DI)
unnamed: U149.1 (DO), U157.3 (DI)
unnamed: U150.1 (DO), U158.3 (DI)
unnamed: U151.1 (DO), U159.3 (DI)
unnamed: U152.1 (DO), U160.3 (DI)
unnamed: U153.1 (DO), U161.3 (DI)
unnamed: U154.1 (DO), U162.3 (DI)
unnamed: U155.1 (DO), U163.3 (DI)
unnamed: U156.1 (DO), U164.3 (DI)
unnamed: U157.1 (DO), U165.3 (DI)
unnamed: U158.1 (DO), U166.3 (DI)

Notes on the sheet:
166 Leds
